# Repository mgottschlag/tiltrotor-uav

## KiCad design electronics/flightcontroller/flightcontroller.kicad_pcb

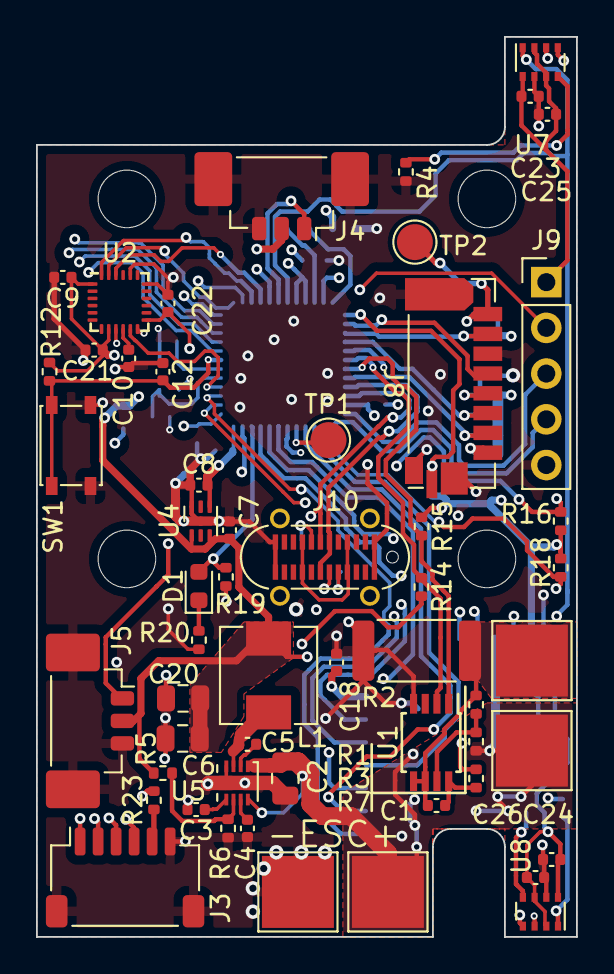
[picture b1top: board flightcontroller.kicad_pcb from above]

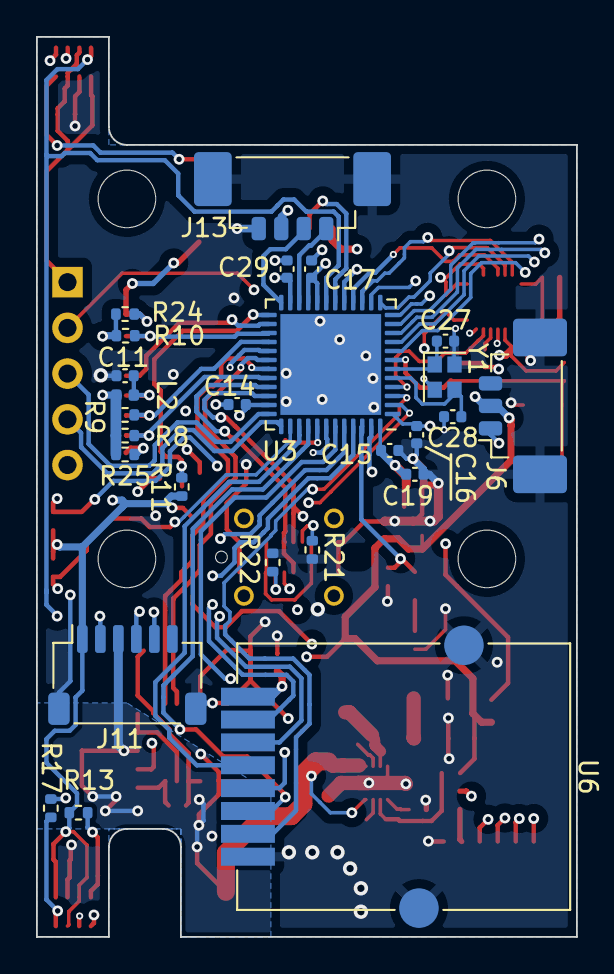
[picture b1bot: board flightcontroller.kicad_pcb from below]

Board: 4 copper layers, 30.0 x 50.0 mm, 85 parts (26 on the bottom side), 65 nets.

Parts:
C1, C5, C9, C10, C12, C14, C15, C16, C21, C22, C29: 0.1uF; C_0402_1005Metric
C2: 10uF/25V; C_0805_2012Metric
C3: 3300pF; C_0402_1005Metric
C4: 1uF/10V; C_0402_1005Metric
C6, C20: 22uF/6.3V; C_0805_2012Metric
C7: 1uF/25V; C_0402_1005Metric
C8, C11, C18, C19, C23, C24, C25, C26: 10uF/6.3V; C_0402_1005Metric
C17: 10uF; C_0402_1005Metric
C27, C28: 6.8pF; C_0402_1005Metric
D1: LED; LED_0603_1608Metric
H1, H2, H3, H4: MountingHole; MountingHole_3.2mm_M3_ISO7380
J1: BAT+; TestPoint_Pad_4.0x4.0mm
J2: ESC+; TestPoint_Pad_4.0x4.0mm
J3: ESC; JST_SH_SM06B-SRSS-TB_1x06-1MP_P1.00mm_Horizontal
J4: Servo3; Molex_PicoBlade_53398-0371_1x03-1MP_P1.25mm_Vertical
J5: Servo2; Molex_PicoBlade_53398-0371_1x03-1MP_P1.25mm_Vertical
J6: Servo1; Molex_PicoBlade_53398-0371_1x03-1MP_P1.25mm_Vertical
J7: ESC-; TestPoint_Pad_4.0x4.0mm
J8: Micro_SD_Card_Det_HYC80-TF08-XXX; HYC80-TF08-XXX
J9: SWD; PinHeader_1x05_P2.54mm_Vertical
J10: USB; USB_C_Receptacle_Amphenol_12402032
J11: Payload; JST_SH_SM06B-SRSS-TB_1x06-1MP_P1.00mm_Horizontal
J12: BAT-; TestPoint_Pad_4.0x4.0mm
J13: Conn_01x04; Molex_PicoBlade_53398-0471_1x04-1MP_P1.25mm_Vertical
L1: 3.3uH; L_AVX_LMLP0506D
L2: 600R@100MHz; L_0402_1005Metric
R1, R4, R12, R13, R17: 10k; R_0402_1005Metric
R2: 0.001; R_2512_6332Metric
R3: 20k; R_0402_1005Metric
R5: 68k; R_0402_1005Metric
R6: 16k; R_0402_1005Metric
R7: 470; R_0402_1005Metric
R8, R9, R10, R11, R19, R24, R25: 47k; R_0402_1005Metric
R14, R15, R16, R18: 4.7k; R_0402_1005Metric
R20: 1k; R_0402_1005Metric
R21, R22: 5.1k; R_0402_1005Metric
R23: DNP; R_0402_1005Metric
SW1: RESET; SW_SPST_PTS815
TP1: SWO; TestPoint_Pad_D2.0mm
TP2: DAT1; TestPoint_Pad_D2.0mm
U1: DS2745U; TSSOP-8_3x3mm_P0.65mm
U2: MPU-9250; InvenSense_QFN-24_3x3mm_P0.4mm
U3: STM32G491CCUx; QFN-48-1EP_7x7mm_P0.5mm_EP5.6x5.6mm
U4: MIC5514-3.3; MLF-6-1EP_1.6x1.6mm_P0.5mm_EP0.5x1.26mm
U5: BD9D322QWZ; Rohm_BD9D322QWZ
U6: GT-24-Mini
U7, U8: Omron_2SMPB-02B; Omron_2SMPB
Y1: 24MHz; Crystal_SMD_2016-4Pin_2.0x1.6mm

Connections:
+3V3: C8.2, C9.1, C14.1, C15.1, C16.1, C17.1, C18.1, C19.1, C21.1, C22.1, C23.1, C24.1, C25.1, C26.1, C29.1, J9.1, J11.1, J13.3, L2.2, R8.1, R9.1, R10.1, R11.1, R12.1, R13.1, R14.1, R15.1, R16.1, R18.1, R23.2, R24.1, R25.1, U2.1 (RESV_VDDIO), U2.8 (VDDIO), U2.13 (VDD), U3.1 (VBAT), U3.20 (VREF+), U3.21 (VDDA), U3.23 (VDD), U3.35 (VDD), U3.48 (VDD), U4.4 (VOUT), U6.1 (VCC), U7.2 (~CS/VDDIO), U7.6 (VDDIO), U7.8 (VDD), U8.2 (~CS/VDDIO), U8.6 (VDDIO), U8.8 (VDD)
+4V: C6.2, C7.1, C20.2, J4.2, J5.2, J6.2, J11.2, L1.2, R5.1, R7.2, U4.1 (EN), U4.3 (VIN)
+BATT: C2.2, J1.1, J2.1, J11.3, R3.2, U5.1 (VIN), U5.8 (EN)
/MCU/GPS_RX: J13.2, U3.24 (PB11)
/MCU/GPS_TX: J13.1, U3.22 (PB10)
/MCU/IMU_FSYNC: U2.11 (FSYNC), U3.4 (PC15)
/MCU/IMU_INT: U2.12 (INT), U3.12 (PA4)
/MCU/IMU_MISO: U2.9 (AD0/MISO), U3.14 (PA6)
/MCU/IMU_MOSI: U2.24 (SDA/MOSI), U3.15 (PA7)
/MCU/IMU_SCLK: U2.23 (SCL/SCLK), U3.13 (PA5)
/MCU/IMU_~CS: U2.22 (~CS), U3.16 (PC4)
/MCU/OSCA: C27.1, U3.6 (PF1), Y1.1
/MCU/OSCB: C28.1, U3.5 (PF0), Y1.3
/MCU/PAYLOAD_RX: J11.5, U3.45 (PB7)
/MCU/PAYLOAD_TX: J11.4, U3.44 (PB6)
/MCU/PR_RST: R17.1, U3.19 (PB2), U7.1 (RST), U8.1 (RST)
/MCU/PR_SCL: R18.2, U3.38 (PA15), U7.4 (SCK/SCL), U8.4 (SCK/SCL)
/MCU/PR_SDA: R16.2, U3.47 (PB9), U7.3 (SDI/SDA), U8.3 (SDI/SDA)
/MCU/PWM_M1: J3.4, U3.8 (PA0)
/MCU/PWM_M2: J3.3, U3.9 (PA1)
/MCU/PWM_M3: J3.2, U3.10 (PA2)
/MCU/PWM_M4: J3.1, U3.11 (PA3)
/MCU/PWR_SCL: R15.2, U1.1 (SCL), U3.31 (PA9)
/MCU/PWR_SDA: R14.2, U1.2 (SDA), U3.30 (PA8)
/MCU/RADIO_CE: U3.2 (PC13), U6.2 (CE)
/MCU/RADIO_MISO: U3.40 (PC11), U6.6 (MISO)
/MCU/RADIO_MOSI: U3.43 (PB5), U6.5 (MOSI)
/MCU/RADIO_SCK: U3.39 (PC10), U6.4 (SCK)
/MCU/RADIO_~CS: U3.29 (PC6), U6.3 (~CS)
/MCU/RADIO_~IRQ: U3.3 (PC14), U6.7 (~IRQ)
/MCU/SD_CS: J8.2 (DAT3/CD), R8.2, U3.32 (PA10)
/MCU/SD_DET: J8.9 (DET1), R11.2, U3.25 (PB12)
/MCU/SD_MISO: J8.7 (DAT0), R10.2, U3.27 (PB14)
/MCU/SD_MOSI: J8.3 (CMD), R9.2, U3.28 (PB15)
/MCU/SD_SCK: J8.5 (CLK), U3.26 (PB13)
/MCU/SERVO_ELEV: J4.1, U3.18 (PB1)
/MCU/SERVO_ENG: J5.1, U3.42 (PB4)
/MCU/SERVO_RUD: J6.1, U3.17 (PB0)
/MCU/SWCLK: J9.4, U3.37 (PA14)
/MCU/SWDIO: J9.3, U3.36 (PA13)
/MCU/SWO: TP1.1, U3.41 (PB3)
/MCU/USBN: J10.A7 (D-), J10.B7 (D-), U3.33 (PA11)
/MCU/USBP: J10.A6 (D+), J10.B6 (D+), U3.34 (PA12)
/MCU/~RESET: C12.1, J9.2, R12.2, SW1.1, U3.7 (PG10)
/Power Management/-BATT: C1.2, J12.1, R1.1, R2.1, U1.5 (VSS), U1.6 (CTG)
GND: C2.1, C3.2, C4.2, C6.1, C7.2, C8.1, C9.2, C10.2, C11.2, C12.2, C14.2, C15.2, C16.2, C17.2, C18.2, C19.2, C20.1, C21.2, C22.2, C23.2, C24.2, C25.2, C26.2, C27.2, C28.2, C29.2, J3.6, J3.MP (MountPin), J4.3, J4.MP (MountPin), J5.3, J5.MP (MountPin), J6.3, J6.MP (MountPin), J7.1, J8.6 (VSS), J8.10 (DET2), J8.11 (SHIELD), J9.5, J10.A1 (GND), J10.A12 (GND), J10.B1 (GND), J10.B12 (GND), J11.6, J11.MP (MountPin), J13.4, J13.MP (MountPin), R2.2, R4.2, R6.2, R17.2, R19.2, R20.2, R21.1, R22.1, SW1.2, U1.4 (SNS), U2.18 (GND), U2.20 (RESV_GND), U3.49 (VSS), U4.6 (GND), U4.7 (EP), U5.4 (GND), U5.9 (EP), U6.8 (GND), U6.9 (GND), U6.10 (GND), U7.7 (GND), U8.7 (GND), Y1.2, Y1.4
unnamed: C1.1, R7.1, U1.8 (VDD)
unnamed: C3.1, U5.5 (SS)
unnamed: C4.1, U5.7 (VREG)
unnamed: C5.1, U5.2 (BOOT)
unnamed: C5.2, L1.1, U5.3 (SW)
unnamed: C10.1, U2.10 (REGOUT)
unnamed: C11.1, J8.4 (VDD), L2.1
unnamed: D1.1 (K), R20.1
unnamed: D1.2 (A), R19.1, U3.46 (PB8)
unnamed: J3.5, R23.1
unnamed: J8.1 (DAT2), R25.2
unnamed: J8.8 (DAT1), R24.2, TP2.1
unnamed: J10.A4 (VBUS), J10.A9 (VBUS), J10.B4 (VBUS), J10.B9 (VBUS)
unnamed: J10.A5 (CC1), R22.2
unnamed: J10.B5 (CC2), R21.2
unnamed: R1.2, R3.1, U1.7 (VIN)
unnamed: R4.1, U7.5 (SDO/ADDR)
unnamed: R5.2, R6.1, U5.6 (FB)
unnamed: R13.2, U8.5 (SDO/ADDR)

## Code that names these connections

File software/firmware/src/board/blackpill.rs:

use super::{Direction, EnginePwm};

use cortex_m::prelude::_embedded_hal_blocking_delay_DelayUs;
use defmt::info;
use embassy_stm32::adc::Adc;
use embassy_stm32::adc::VrefInt;
use embassy_stm32::gpio::{Level, Output, OutputType, Speed};
use embassy_stm32::i2c::I2c;
use embassy_stm32::mode::Async;
use embassy_stm32::peripherals::{ADC1, PA0, PA1, PA2, PA3, PA4, PB3, PB4, PB5, PB8, PB9, TIM5};
use embassy_stm32::spi::Config as SpiConfig;
use embassy_stm32::spi::Spi;
use embassy_stm32::time::hz;
use embassy_stm32::timer::simple_pwm::{PwmPin, SimplePwm};
use embassy_stm32::usart;
use embassy_stm32::usart::Config;
use embassy_stm32::usart::Parity;
use embassy_stm32::usart::StopBits;
use embassy_stm32::usart::Uart;
use embassy_stm32::{bind_interrupts, i2c, peripherals};
use embassy_time::Delay;
use libm::fabs;
use motor::Command;

type PwmC1 = PA0;
type PwmC2 = PA1;
type RadioRx = PA3;
type RadioTx = PA2;
type StorageSck = PB3;
type StorageMiso = PB4;
type StorageMosi = PB5;
type DisplaySck = PB8;
type DisplaySda = PB9;
// type ImuSck = PB13;
// type ImuMiso = PB14;
// type ImuMosi = PB15;
type EngineInt1 = Output<'static>; // PB2
type EngineInt2 = Output<'static>; // PC13
type EngineInt3 = Output<'static>; // PC14
type EngineInt4 = Output<'static>; // PC15

pub type DisplayI2c = I2c<'static, Async>;
pub type RadioUart = Uart<'static, Async>; // USART2
pub type StorageCs = Output<'static>;
pub type StorageSpi = Spi<'static, Async>; // SPI3

bind_interrupts!(struct Irqs {
    I2C1_EV => i2c::EventInterruptHandler<peripherals::I2C1>;
    I2C1_ER => i2c::ErrorInterruptHandler<peripherals::I2C1>;
    USART2 => usart::InterruptHandler<peripherals::USART2>;
});

pub struct Board<M: motor::Type> {
    pub display_i2c: DisplayI2c,
    pub engines: BlackpillEnginePwm<M>,
    pub radio_uart: RadioUart,
    pub battery_monitor: BatteryMonitor,
    pub storage_spi: StorageSpi,
    pub storage_cs: StorageCs,
}

impl<M: motor::Type> Board<M> {
    pub fn init(motor_driver: M) -> Board<M> {
        let p = embassy_stm32::init(Default::default());

        // init display
        let display_sck: DisplaySck = p.PB8;
        let display_sda: DisplaySda = p.PB9;
        let display_i2c = I2c::new(
            p.I2C1,
            display_sck,
            display_sda,
            Irqs,
            p.DMA1_CH1,
            p.DMA1_CH0,
            hz(400_000),
            Default::default(),
        );

        // init battery adc
        let battery_delay = Delay;
        let battery_adc = Adc::new(p.ADC1);
        let battery_monitor = BatteryMonitor::init(battery_adc, battery_delay, p.PA4);

        // init storage
        let mut storage_spi_config = SpiConfig::default();
        storage_spi_config.frequency = hz(250_000); // TODO: 1_000_000 or more?

        let storage_sck: StorageSck = p.PB3;
        let storage_miso: StorageMiso = p.PB4;
        let storage_mosi: StorageMosi = p.PB5;
        let storage_cs: StorageCs = Output::new(p.PA15, Level::High, Speed::VeryHigh);
        let storage_spi = Spi::new(
            p.SPI3,
            storage_sck,
            storage_mosi,
            storage_miso,
            p.DMA1_CH7,
            p.DMA1_CH2,
            storage_spi_config,
        );

        // init pwm
        let pwm_c1: PwmC1 = p.PA0;
        let pwm_c2: PwmC2 = p.PA1;
        let c1 = PwmPin::new_ch1(pwm_c1, OutputType::PushPull);
        let c2 = PwmPin::new_ch2(pwm_c2, OutputType::PushPull);
        let pwm = SimplePwm::new(
            p.TIM5,
            Some(c1),
            Some(c2),
            None,
            None,
            hz(50_000),
            Default::default(),
        );
        let engines = BlackpillEnginePwm::init(
            motor_driver,
            pwm,
            Output::new(p.PB2, Level::Low, Speed::Medium),
            Output::new(p.PC13, Level::Low, Speed::Medium),
            Output::new(p.PC14, Level::Low, Speed::Medium),
            Output::new(p.PC15, Level::Low, Speed::Medium),
        );

        // init radio
        let mut radio_uart_config = Config::default();
        radio_uart_config.baudrate = 100000;
        radio_uart_config.parity = Parity::ParityEven;
        radio_uart_config.stop_bits = StopBits::STOP2;
        let radio_rx: RadioRx = p.PA3;
        let radio_tx: RadioTx = p.PA2;
        let radio_uart = Uart::new(
            p.USART2,
            radio_rx,
            radio_tx,
            Irqs,
            p.DMA1_CH6,
            p.DMA1_CH5,
            radio_uart_config,
        )
        .unwrap();

        Board {
            display_i2c,
            engines,
            radio_uart,
            battery_monitor,
            storage_spi,
            storage_cs,
        }
    }
}

pub type EnginePwmType<M> = BlackpillEnginePwm<M>;

const MINIMAL_DUTY: u16 = 150;

pub struct BlackpillEnginePwm<M>
where
    M: motor::Type,
{
    motor_driver: M,
    pwm: SimplePwm<'static, TIM5>,
    int1: EngineInt1,
    int2: EngineInt2,
    int3: EngineInt3,
    int4: EngineInt4,
}

impl<M> BlackpillEnginePwm<M>
where
    M: motor::Type,
{
    pub fn init(
        motor_driver: M,
        mut pwm: SimplePwm<'static, TIM5>,
        int1: EngineInt1,
        int2: EngineInt2,
        int3: EngineInt3,
        int4: EngineInt4,
    ) -> Self {
        pwm.ch1().set_duty_cycle(0);
        pwm.ch2().set_duty_cycle(0);
        pwm.ch1().enable();
        pwm.ch2().enable();
        BlackpillEnginePwm {
            motor_driver,
            pwm,
            int1,
            int2,
            int3,
            int4,
        }
    }

    fn get_max_duty(&self) -> u16 {
        self.pwm.max_duty_cycle()
    }

    fn scale_duty(&self, duty: f32) -> u16 {
        if duty == 0.0 {
            return 0;
        } else {
            return ((self.get_max_duty() - MINIMAL_DUTY) as f32 * duty) as u16 + MINIMAL_DUTY;
        }
    }

    fn set_duty(&mut self, duty: [f32; 2]) {
        let scaled_duty = duty.map(|d| {
            self.scale_duty(fabs(d as f64) as f32)
                .clamp(0, self.get_max_duty())
        });
        info!(
            "duty={} => scaled_duty={} ({})",
            duty,
            scaled_duty,
            self.pwm.max_duty_cycle()
        );
        self.pwm.ch1().set_duty_cycle(scaled_duty[0]);
        self.pwm.ch2().set_duty_cycle(scaled_duty[1]);
    }
}

impl<M: motor::Type> EnginePwm for BlackpillEnginePwm<M> {
    fn update(&mut self, cmd: &Command) {
        let directions = self.motor_driver.translate(cmd);
        info!(
            "motor_left={:?}, motor_right={:?}",
            directions[0], directions[1]
        );

        let mut duty_left = 0.0;
        let mut duty_right = 0.0;

        match directions[0] {
            Direction::Forward(duty) => {
                self.int1.set_high();
                self.int2.set_low();
                duty_left = duty;
            }
            Direction::Backward(duty) => {
                self.int1.set_low();
                self.int2.set_high();
                duty_left = duty;
            }
            Direction::Stop => {
                self.int1.set_low();
                self.int2.set_low();
            }
        }
        match directions[1] {
            Direction::Forward(duty) => {
                self.int3.set_low();
                self.int4.set_high();
                duty_right = duty;
            }
            Direction::Backward(duty) => {
                self.int3.set_high();
                self.int4.set_low();
                duty_right = duty;
            }
            Direction::Stop => {
                self.int3.set_low();
                self.int4.set_low();
            }
        }

        self.set_duty([duty_left, duty_right]);
    }
}

pub struct BatteryMonitor {
    adc: Adc<'static, ADC1>,
    pin: PA4,
}

impl BatteryMonitor {
    pub fn init(adc: Adc<'static, ADC1>, mut delay: Delay, pin: PA4) -> Self {
        adc.enable_vrefint();
        delay.delay_us(VrefInt::start_time_us());
        Self { adc, pin }
    }

    pub fn read(&mut self) -> f32 {
        let v = self.adc.blocking_read(&mut self.pin) as f32;
        v * 996.0 / 274.4 / 1000.0
    }
}

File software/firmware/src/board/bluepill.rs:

use embedded_hal::PwmPin;
use pac::{SPI2, TIM2};
use stm32f1xx_hal::gpio::gpioa::{PA8, PA9};
use stm32f1xx_hal::gpio::gpiob::{PB12, PB13, PB14, PB15};
use stm32f1xx_hal::gpio::{Alternate, Floating, IOPinSpeed, Input, Output, OutputSpeed, PushPull};
use stm32f1xx_hal::prelude::*;
use stm32f1xx_hal::pwm::{PwmChannel, C1, C2, C3, C4};
use stm32f1xx_hal::spi::{self, Phase, Polarity, Spi, Spi2NoRemap};
pub use stm32f1xx_hal::stm32 as pac;
use stm32f1xx_hal::time::U32Ext;
use stm32f1xx_hal::timer::{Tim2NoRemap, Timer};

use super::EnginePwm;

pub type RadioSck = PB13<Alternate<PushPull>>;
pub type RadioMiso = PB14<Input<Floating>>;
pub type RadioMosi = PB15<Alternate<PushPull>>;
pub type RadioCs = PA8<Output<PushPull>>;
pub type RadioCe = PA9<Output<PushPull>>;
pub type RadioIrq = PB12<Output<PushPull>>;
pub type RadioSpi = Spi<SPI2, Spi2NoRemap, (RadioSck, RadioMiso, RadioMosi), u8>;

pub struct Board {
    pub engines: BluepillEnginePwm,
    pub radio_spi: RadioSpi,
    pub radio_cs: RadioCs,
    pub radio_ce: RadioCe,
    pub radio_irq: RadioIrq,
}

impl Board {
    pub fn init(_core: rtic::Peripherals, device: pac::Peripherals) -> Board {
        let mut flash = device.FLASH.constrain();
        let rcc = device.RCC.constrain();
        let mut afio = device.AFIO.constrain();

        let clocks = rcc
            .cfgr
            .use_hse(8.mhz())
            .sysclk(48.mhz())
            .pclk1(24.mhz())
            .freeze(&mut flash.acr);

        let mut gpioa = device.GPIOA.split();
        let mut gpiob = device.GPIOB.split();

        // Engine PWM:
        let c1 = gpioa.pa0.into_alternate_push_pull(&mut gpioa.crl);
        let c2 = gpioa.pa1.into_alternate_push_pull(&mut gpioa.crl);
        let c3 = gpioa.pa2.into_alternate_push_pull(&mut gpioa.crl);
        let c4 = gpioa.pa3.into_alternate_push_pull(&mut gpioa.crl);
        let pins = (c1, c2, c3, c4);
        let pwm = Timer::tim2(device.TIM2, &clocks).pwm::<Tim2NoRemap, _, _, _>(
            pins,
            &mut afio.mapr,
            50.hz(),
        );

        let engines = BluepillEnginePwm::init(pwm.split());

        // radio
        let mut radio_cs = gpioa.pa8.into_push_pull_output(&mut gpioa.crh);
        let mut radio_ce = gpioa.pa9.into_push_pull_output(&mut gpioa.crh);
        let mut radio_irq = gpiob.pb12.into_push_pull_output(&mut gpiob.crh);
        let mut radio_sck = gpiob.pb13.into_alternate_push_pull(&mut gpiob.crh);
        let radio_miso = gpiob.pb14.into_floating_input(&mut gpiob.crh);
        let mut radio_mosi = gpiob.pb15.into_alternate_push_pull(&mut gpiob.crh);

        radio_cs.set_speed(&mut gpioa.crh, IOPinSpeed::Mhz50);
        radio_ce.set_speed(&mut gpioa.crh, IOPinSpeed::Mhz50);
        radio_irq.set_speed(&mut gpiob.crh, IOPinSpeed::Mhz50);
        radio_sck.set_speed(&mut gpiob.crh, IOPinSpeed::Mhz50);
        radio_mosi.set_speed(&mut gpiob.crh, IOPinSpeed::Mhz50);

        let radio_spi = Spi::spi2(
            device.SPI2,
            (radio_sck, radio_miso, radio_mosi),
            spi::Mode {
                polarity: Polarity::IdleLow,
                phase: Phase::CaptureOnFirstTransition,
            },
            2.mhz(),
            clocks,
        );

        Board {
            engines,
            radio_spi,
            radio_cs,
            radio_ce,
            radio_irq,
        }
    }
}

pub type EnginePwmType = BluepillEnginePwm;

pub struct BluepillEnginePwm {
    c: (
        PwmChannel<TIM2, C1>,
        PwmChannel<TIM2, C2>,
        PwmChannel<TIM2, C3>,
        PwmChannel<TIM2, C4>,
    ),
}

impl BluepillEnginePwm {
    pub fn init(
        mut c: (
            PwmChannel<TIM2, C1>,
            PwmChannel<TIM2, C2>,
            PwmChannel<TIM2, C3>,
            PwmChannel<TIM2, C4>,
        ),
    ) -> Self {
        c.0.set_duty(0);
        c.1.set_duty(0);
        c.2.set_duty(0);
        c.3.set_duty(0);
        c.0.enable();
        c.1.enable();
        c.2.enable();
        c.3.enable();
        BluepillEnginePwm { c }
    }
}

impl EnginePwm for BluepillEnginePwm {
    fn get_max_duty(&self) -> u16 {
        // We assume that all channels have the same maximum duty.
        self.c.0.get_max_duty()
    }
    fn set_duty(&mut self, duty: [u16; 4]) {
        self.c.0.set_duty(duty[0]);
        self.c.1.set_duty(duty[1]);
        self.c.2.set_duty(duty[2]);
        self.c.3.set_duty(duty[3]);
    }
}

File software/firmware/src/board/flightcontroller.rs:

use super::EscDriver;

use embassy_stm32::Peri;
use embassy_stm32::gpio::Level;
use embassy_stm32::gpio::Output;
use embassy_stm32::gpio::OutputType;
use embassy_stm32::gpio::Speed;
use embassy_stm32::mode::Async;
use embassy_stm32::peripherals::USB_OTG_FS;
use embassy_stm32::peripherals::{PA5, PA6, PA7, PA9, PA10, TIM3, TIM5};
use embassy_stm32::spi::Config as SpiConfig;
use embassy_stm32::spi::Spi;
use embassy_stm32::time::Hertz;
use embassy_stm32::time::hz;
use embassy_stm32::timer::simple_pwm::PwmPin;
use embassy_stm32::timer::simple_pwm::SimplePwm;
use embassy_stm32::usart;
use embassy_stm32::usart::Config as UsartConfig;
use embassy_stm32::usart::HalfDuplexReadback;
use embassy_stm32::usart::Parity;
use embassy_stm32::usart::StopBits;
use embassy_stm32::usart::Uart;
use embassy_stm32::usb;
use embassy_stm32::{bind_interrupts, i2c, peripherals};
use embassy_usb::Builder;
use embassy_usb::class::cdc_acm::CdcAcmClass;
use embassy_usb::class::cdc_acm::State;
use static_cell::StaticCell;

// see https://github.com/betaflight/unified-targets/blob/master/configs/default/OPEN-REVO.config for pin map
// or  https://www.getfpv.com/lumenier-skitzo-flight-controller-powered-by-flightone.html for some general information
type RadioRx = Peri<'static, PA10>;
type RadioTx = Peri<'static, PA9>;
type ImuSck = Peri<'static, PA5>;
type ImuMiso = Peri<'static, PA6>;
type ImuMosi = Peri<'static, PA7>;

pub type ImuSpi = Spi<'static, Async>; // SPI1
pub type ImuCs = Output<'static>; // PA4
pub type RadioUart = Uart<'static, Async>; // USART1
pub type UsbClass = CdcAcmClass<'static, usb::Driver<'static, USB_OTG_FS>>;
pub type UsbDevice = embassy_usb::UsbDevice<'static, usb::Driver<'static, USB_OTG_FS>>;
pub type UsbReceiver =
    embassy_usb::class::cdc_acm::Receiver<'static, usb::Driver<'static, USB_OTG_FS>>;
pub type UsbSender = embassy_usb::class::cdc_acm::Sender<'static, usb::Driver<'static, USB_OTG_FS>>;
pub type EscDriverType = BlackpillEscDriver;

bind_interrupts!(struct Irqs {
    I2C1_EV => i2c::EventInterruptHandler<peripherals::I2C1>;
    I2C1_ER => i2c::ErrorInterruptHandler<peripherals::I2C1>;
    OTG_FS => usb::InterruptHandler<peripherals::USB_OTG_FS>;
    USART1 => usart::InterruptHandler<peripherals::USART1>;
});

static EP_OUT_BUFFER: StaticCell<[u8; 256]> = StaticCell::new();
static CONFIG_DESCRIPTOR: StaticCell<[u8; 256]> = StaticCell::new();
static BOS_DESCRIPTOR: StaticCell<[u8; 256]> = StaticCell::new();
static CONTROL_BUF: StaticCell<[u8; 64]> = StaticCell::new();
static STATE: StaticCell<State> = StaticCell::new();

pub struct Board {
    pub radio_uart: RadioUart,
    pub imu_spi: ImuSpi,
    pub imu_cs: ImuCs,
    pub usb_class: UsbClass,
    pub usb_device: UsbDevice,
    pub esc_driver: EscDriverType,
}

impl Board {
    pub fn init() -> Board {
        let mut config = embassy_stm32::Config::default();
        {
            use embassy_stm32::rcc::*;
            config.rcc.hse = Some(Hse {
                freq: Hertz(8_000_000),
                mode: HseMode::Oscillator,
            });
            config.rcc.pll_src = PllSource::HSE;
            config.rcc.pll = Some(Pll {
                prediv: PllPreDiv::DIV8,
                mul: PllMul::MUL336,
                divp: Some(PllPDiv::DIV2), // 8mhz / 4 * 168 / 2 = 168Mhz.
                divq: Some(PllQDiv::DIV7), // 8mhz / 4 * 168 / 7 = 48Mhz.
                divr: None,
            });
            config.rcc.ahb_pre = AHBPrescaler::DIV1;
            config.rcc.apb1_pre = APBPrescaler::DIV4;
            config.rcc.apb2_pre = APBPrescaler::DIV2;
            config.rcc.sys = Sysclk::PLL1_P;
            config.rcc.mux.clk48sel = mux::Clk48sel::PLL1_Q;
        }
        let p = embassy_stm32::init(config);

        // init usb connection
        let ep_out_buffer = EP_OUT_BUFFER.init([0; 256]);
        let config_descriptor = CONFIG_DESCRIPTOR.init([0; 256]);
        let bos_descriptor = BOS_DESCRIPTOR.init([0; 256]);
        let control_buf = CONTROL_BUF.init([0; 64]);
        let state = STATE.init(State::new());

        let mut config = usb::Config::default();
        config.vbus_detection = false;
        let driver = usb::Driver::new_fs(p.USB_OTG_FS, Irqs, p.PA12, p.PA11, ep_out_buffer, config);

        let mut config = embassy_usb::Config::new(0xdead, 0xcafe);
        config.manufacturer = Some("Instinctive Llama Solutions");
        config.product = Some("UAV");
        config.serial_number = Some("42");

        let mut usb_builder = Builder::new(
            driver,
            config,
            config_descriptor,
            bos_descriptor,
            &mut [],
            control_buf,
        );

        let usb_class = CdcAcmClass::new(&mut usb_builder, state, 64);
        let usb_device = usb_builder.build();

        // init radio
        let mut radio_uart_config = UsartConfig::default();
        radio_uart_config.baudrate = 100000;
        radio_uart_config.parity = Parity::ParityEven;
        radio_uart_config.stop_bits = StopBits::STOP2;
        let _radio_rx: RadioRx = p.PA10;
        let radio_tx: RadioTx = p.PA9;
        let radio_uart = Uart::new_half_duplex(
            p.USART1,
            radio_tx,
            Irqs,
            p.DMA2_CH7,
            p.DMA2_CH2,
            radio_uart_config,
            HalfDuplexReadback::Readback,
        )
        .unwrap();

        // init imu
        let imu_cs = Output::new(p.PA4, Level::High, Speed::VeryHigh);
        let imu_sck: ImuSck = p.PA5;
        let imu_miso: ImuMiso = p.PA6;
        let imu_mosi: ImuMosi = p.PA7;
        let mut imu_spi_config = SpiConfig::default();
        imu_spi_config.frequency = hz(1_000_000);
        let imu_spi = Spi::new(
            p.SPI1,
            imu_sck,
            imu_mosi,
            imu_miso,
            p.DMA2_CH3,
            p.DMA2_CH0,
            imu_spi_config,
        );

        // init esc driver
        let pwm_tim5 = SimplePwm::new(
            p.TIM5,
            Some(PwmPin::new(p.PA0, OutputType::PushPull)),
            None,
            Some(PwmPin::new(p.PA2, OutputType::PushPull)),
            None,
            hz(50),
            Default::default(),
        );
        let pwm_tim3 = SimplePwm::new(
            p.TIM3,
            None,
            None,
            Some(PwmPin::new(p.PB0, OutputType::PushPull)),
            Some(PwmPin::new(p.PB1, OutputType::PushPull)),
            hz(50),
            Default::default(),
        );
        let esc_driver = BlackpillEscDriver::init(pwm_tim5, pwm_tim3);

        Board {
            radio_uart,
            imu_spi,
            imu_cs,
            usb_class,
            usb_device,
            esc_driver,
        }
    }
}

pub struct BlackpillEscDriver {
    pwm_tim5: SimplePwm<'static, TIM5>,
    pwm_tim3: SimplePwm<'static, TIM3>,
    offset_tim5: u16,
    offset_tim3: u16,
}

impl BlackpillEscDriver {
    /// Create the ESC PWM driver for Blackpill.
    ///
    /// M1: PB0
    /// M2: PB1
    /// M3: PA0 (TX4, M3 seems to be broken on flightcontroller board)
    /// M4: PA2
    pub fn init(
        mut pwm_tim5: SimplePwm<'static, TIM5>,
        mut pwm_tim3: SimplePwm<'static, TIM3>,
    ) -> Self {
        {
            pwm_tim5.ch1().enable();
            pwm_tim5.ch3().enable();
        }
        {
            pwm_tim3.ch3().enable();
            pwm_tim3.ch4().enable();
        }
        let offset_tim5 = (pwm_tim5.max_duty_cycle() as f32 * 0.05) as u16;
        let offset_tim3 = (pwm_tim3.max_duty_cycle() as f32 * 0.05) as u16;
        Self {
            pwm_tim5,
            pwm_tim3,
            offset_tim5,
            offset_tim3,
        }
    }
}

impl EscDriver for BlackpillEscDriver {
    fn update(&mut self, thrust: [f32; 4]) {
        // M1 (PB0 @ TIM3)
        self.pwm_tim3
            .ch3()
            .set_duty_cycle(calc(thrust[0], self.offset_tim3));
        // M2 (PB1 @ TIM3)
        self.pwm_tim3
            .ch4()
            .set_duty_cycle(calc(thrust[1], self.offset_tim3));
        // M3 (PA0 @ TIM5)
        self.pwm_tim5
            .ch1()
            .set_duty_cycle(calc(thrust[2], self.offset_tim5));
        // M4 (PA2 @ TIM5)
        self.pwm_tim5
            .ch3()
            .set_duty_cycle(calc(thrust[3], self.offset_tim5));
    }
}

fn calc(input: f32, offset: u16) -> u16 {
    let clamped = f32::max(f32::min(input, 1.0), 0.0);
    (clamped * offset as f32) as u16 + offset
}

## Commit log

2021-07-04 Initial import of a design document.
2021-07-04 Add two possible configurations
2021-07-04 Add .gitignore
2021-07-09 Added a firmware class diagram.
2021-07-11 Add an empty cargo project for the flight control firmware.
2021-07-11 Modify the firmware project to support multiple hardware platforms.
2021-07-18 Add documentation of the aerodynamic pre-design
2021-07-25 firmware: Add some bluepill PWM code for engine control.
2021-07-30 Build bluepill
2021-07-30 rustup
2021-07-30 rustup target add thumbv7m-none-eabi
2021-07-30 jobs
2021-07-30 project
2021-07-30 Inntroduce Travis Builds (#1)
2021-07-30 [firmware] Implement PWM for blackpill
2021-07-30 [firmware] Implement PWM for blackpill (#2)
2021-08-12 Implement radio via nrf24l01
2021-08-14 First parts of the PCB design: Power supply and monitoring.
2021-08-16 Review
2021-08-17 Bluepill: update IRQ pin
2021-08-18 return
2021-08-18 Implement radio via nrf24l01 (#3)
2021-08-18 [firmware] Fix typo in comment
2021-08-21 electronics: Draft most of the flight controller schematics.
    The power supply part is not complete, and all connections to the MCU are
    missing.
2021-08-21 electronics: Changed the 4V regulator and added some ordering codes.
2021-09-01 PCB: Added missing footprints and an SD card slot symbol.
2021-09-01 PCB: USB, micro SD, and many component changes.
2021-09-02 electronics: General PCB layout and size, let pressure sensors use I2C.
2021-09-03 electronics: Microcontroller connections, general component placement.
2021-09-03 electronics: Fix remaining schematics ERC errors.
2021-09-03 electronics: Fixed the reset switch footprint.
2021-09-04 electronics: Preliminary component placement.
2021-09-25 Switch from stm32f401 to stm32f411
2021-09-25 Switch from stm32f401 to stm32f411 (#4)
2021-09-26 electronics: Finished wiring of the flight controller PCB.
2021-09-26 electronics: Fix most design rule checker errors.
2021-10-10 electronics: Fixed most flightcontroller DRC errors.
2021-10-20 electronics: Add a resistor for ESC power and some test pads.
2021-10-20 electronics: Placed missing resistors and fixed remaining DRC errors.
2021-10-20 electronics: Add a radius to concave outline corners.
2022-01-01 Add files via upload
    Flächen und Leitwerksberechnung
2022-01-22 Update stm32f1xx-hal to '0.8'
2022-01-22 blackpill
2022-01-22 cleanup
2022-01-23 Update stm32f1xx-hal and stm32f4xx-hal to latest versions (#5)
2022-01-24 Support stm32g491 as flightcontroller
2022-01-24 Support stm32g491 as flightcontroller (#6)
2022-01-24 Add CI build job for flightcontroller
2022-01-24 Add CI build job for flightcontroller (#7)
2022-01-24 Introduce RTT for debugging
2022-01-24 Introduce RTT for debugging (#8)
2022-01-25 radio
2022-01-25 more radio
2022-01-25 Handle radio interrupts and return ack payloads
2022-01-25 Drop support for sm32f1xx and stm32f4xx as flightcontroller for now
2022-01-25 Add 'Embed.toml' to allow flashing via cargo-embed
2022-01-25 Drop support for sm32f1xx and stm32f4xx as flightcontroller for now (#9)
2022-01-25 Add 'Embed.toml' to allow flashing via cargo-embed (#10)
2022-01-27 basic remote
2022-01-27 Travis build step
2022-01-27 travis #1
2022-01-27 travis #2
2022-01-27 travis #3
2022-02-03 Refactor radio interrupt
2022-02-07 structopt
2022-02-07 comment
2022-02-07 deserialize
2022-02-07 Control the uav's engines via a basic remote control (#11)
2022-02-07 mpu9250
2022-02-07 delay
2022-02-08 get_rotations
2022-02-08 [firmware] Update rtic to 1.0.0
2022-02-08 [firmware] Update rtic to 1.0.0 (#12)
2022-02-08 task
2022-02-10 stuff
2022-02-12 stabiliztion
2022-02-17 Return rotations
2022-02-17 [firmware] Implement MPU9250 (#13)
2022-02-18 keyevents
2022-02-18 keyevents (#14)
2022-02-21 [firmware] Implement simple PID controller based balancing
2022-02-21 [firmware] Implement simple PID controller based balancing (#15)
2022-02-22 [firmware] Implement pose control via keyboard
2022-02-22 types
2022-02-22 [software] Implement pose control via keyboard (#16)
2024-03-13 firmware: move pid to dedicated file
2024-03-13 Ignore .DS_Store
2024-03-15 Migrate to Embassy and adapt Radio
2024-03-15 remote: move radio to dedicated file
2024-03-16 remote: separate keyboard input from sending commands
2024-03-18 software: update and summarize dependencies
2024-03-18 remote: replace serde_cbor by ciborium
2024-03-19 remote: move keyboard stuff to dedicated file
2024-03-21 remote: add gamepad input
2024-03-22 remote: change minimal command change diff to '20'
2024-03-26 remote: introduce offline mode
2024-03-30 remote: fix gamepad command handling
2024-03-30 firmware: add 'release' to cargo aliases
2024-04-03 protocol: migrate pose vector to f32
2024-04-03 remote: simplify keyboard
2024-04-03 software: drive forward and backward
2024-04-05 firmware: implement basic engine control
2024-04-05 firmware: display status information on ssd1306
2024-04-05 firmware: read battery voltage and show on display
2024-04-05 software: return battery voltage along with status
2024-04-05 firmware: simplify status mutex
2024-04-07 firmware: update engine pin settings
2024-04-07 remote: limit keyboard controlled rotation to 'abs(0.2)'
2024-04-07 firmware: prepare port mappings for storage and imu
2024-04-07 firmware: prepare port mappings pwm channels
2024-04-12 firmware: introduce sdcard-based trace file
2024-04-27 electronics: Production file settings.
2024-05-19 Hide different engine pwm implementations behind trait
2024-05-19 firmware: add error handling for radio
2024-05-24 firmware: add error handling for display
2024-05-24 Less unwraps
2024-05-24 firmware: add error handling for display (#17)
2024-06-05 firmware: update embedded-sdmmc to 0.7.0
2024-06-08 firmware: slightly improve error handling of trace
2024-06-10 firmware: slightly further improve error handling
2024-06-11 softeware: update defmt and defmt-rtt
2024-06-11 software: replace serde_cbor by minicbor
2024-06-20 software: some minor updates
2024-06-20 remote: implement basic resends
2024-06-21 remote: add battery status to ui
2024-06-21 remote: start bevy-driven remote
2024-06-21 remote: migrate offline mode
2024-06-21 remote: reduce bevy feature flags
2024-06-21 remote: reduce bevy feature flags (#18)
2024-06-22 remote: migrate radio resends from old client
2024-06-22 remove old remote
2024-06-22 remote: improve error handling of radio implementation
2025-03-27 firmware: remove outdated platforms
2025-03-27 Gitignore .vscode directories
2025-03-27 firmware: update embassy
2025-03-27 firmware: remove embassy as a submodule
2025-03-27 firmware: migrate to s-bus remote
2025-03-27 software: remove obsolete crates and cleanup feature deps
2025-03-27 firmware: hide device init behind dedicated features
2025-04-03 software: rework creating motor commands
2025-04-03 software: move motor handling to dedicated crate
2025-04-15 firmware: basic motor control
2025-04-17 firmware: cleanup outdated boards
2025-04-20 Prepare directory structure for flightcontroller
2025-06-10 Setup environment to flash flightcontroller to board
2025-06-13 [firmware] Add radio to flightcontroller
2025-06-15 firmware: implement basic usage
2025-11-15 Cleanup some prototype leftovers
2025-11-15 Update embassy dependencies
2025-12-10 Implement very basic stabilizer based on Kf
2025-12-20 firmware: implement basis for usb monitoring connection
2025-12-20 firmware: migrate to rust edition 2024
2025-12-20 firmware: cleanup motor setup
2025-12-20 firmware: remove motor crate
2025-12-20 firmware: add command channel to handle input
2025-12-22 firmware: move protocol to dedicated crate and add serialization
2025-12-22 firmware: add proper vs code settings.json
2025-12-23 firmware: add remote to directly control motors
2025-12-26 firmware: setup pins for motor pwm
2025-12-28 firmware: cleanup oudated crates and tracing
2025-12-28 firmware: find alternative for broken M3 pin
2025-12-28 firmware: set thrust via pwm
2025-12-29 remote: add simple shell
2025-12-29 software: send imu status data to remote
2026-01-13 firmware: actual flight behavior
2026-03-14 more
2026-03-14 software: send imu status data to remote (#19)
2026-03-15 remote: write imu measurements to json file
2026-03-16 Use Github Actions for CI
2026-03-16 Use Github Actions for CI (#20)
2026-03-17 software: improve handling payload length in header
2026-03-22 software: fix transmitting imu debug data via usb
